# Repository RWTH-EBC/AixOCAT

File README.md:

# AixOCAT - Library framework for building automation systems based on the OSCAT libraries

AixOCAT is an open source software library for the implementation of control algorithms in building automation systems and test benches and is based on the [OSCAT](http://www.oscat.de/) libraries.

As the library framework is developed at the [RWTH Aachen University, E.ON Energy Research Center, Institute
for Energy Efficient Buildings and Indoor Climate](https://www.ebc.eonerc.rwth-aachen.de/cms/~dmzz/E-ON-ERC-EBC/?lidx=1), the library's name AixOCAT is derived from the city's French 
name Aix-la-Chapelle, which the people of Aachen are very fond of and use a lot. 
With the name AixOCAT we follow this local tradition.

AixOCAT features support for different software tools, that can be used for the implementation of control algorithms, as well as support for various commonly used communication/signal transmission interfaces.

This GitHub page will be used to further develop the package and make it
available under the
[MIT License](LICENSE).

If you have any questions regarding AixOCAT feel free to contact us at
[ebc-aixocat@eonerc.rwth-aachen.de](mailto:ebc-aixocat@eonerc.rwth-aachen.de).

---

## Description

- Evaluation and interfaces for different tools that can be used for the implementation of control algorithms
- Examples and documentation for different communication/signal transmission interfaces
- General control modules for different use cases 

## Version

AixOCAT is an ongoing research project, the current version is 1.0.0, which is
still a pre-release.

## How to use AixOCAT

### Dependencies

Visual Studio is required.

### Installation Guide

Library Installation in [TwinCAT 3](https://infosys.beckhoff.com/english.php?content=../content/1033/tc3_plc_intro/27021601982523403.html)

Library Installation in [Codesys](https://help.codesys.com/webapp/_cds_struct_installing_libraries;product=codesys;version=3.5.12.0)

If you actively develop AixOCAT you can clone this repository by using:

 `git clone [SSH-Key/Https]`

### How to contribute to the development of AixOCAT
You are invited to contribute to the development of AixOCAT. You may report any issues by using the 
[Issues](https://github.com/RWTH-EBC/AixOCAT/issues) button.
Furthermore, you are welcome to contribute via [Pull Requests](https://github.com/RWTH-EBC/AixOCAT/pulls).
The workflow for changes is described in our [contribution guidelines](CONTRIBUTING.md).

### AixOCAT related publications

- [AixOCAT: Open-Source-Bibliothek für Automationssysteme](Resources/Documentation/AixOCAT_paper_FB_RWTH.pdf)

## License

AixOCAT is released by RWTH Aachen University, E.ON Energy
Research Center, Institute for Energy Efficient Buildings and Indoor Climate,
under the
[MIT License](LICENSE).

## Acknowledgements

As this framework is based on the OSCAT libraries we want to acknowlegde Tobias Mühlbauer for his Contribution to the OSCAT libraries.

We also acknowledge the ERDF for their financial support (reference No. KEU-1-006C).

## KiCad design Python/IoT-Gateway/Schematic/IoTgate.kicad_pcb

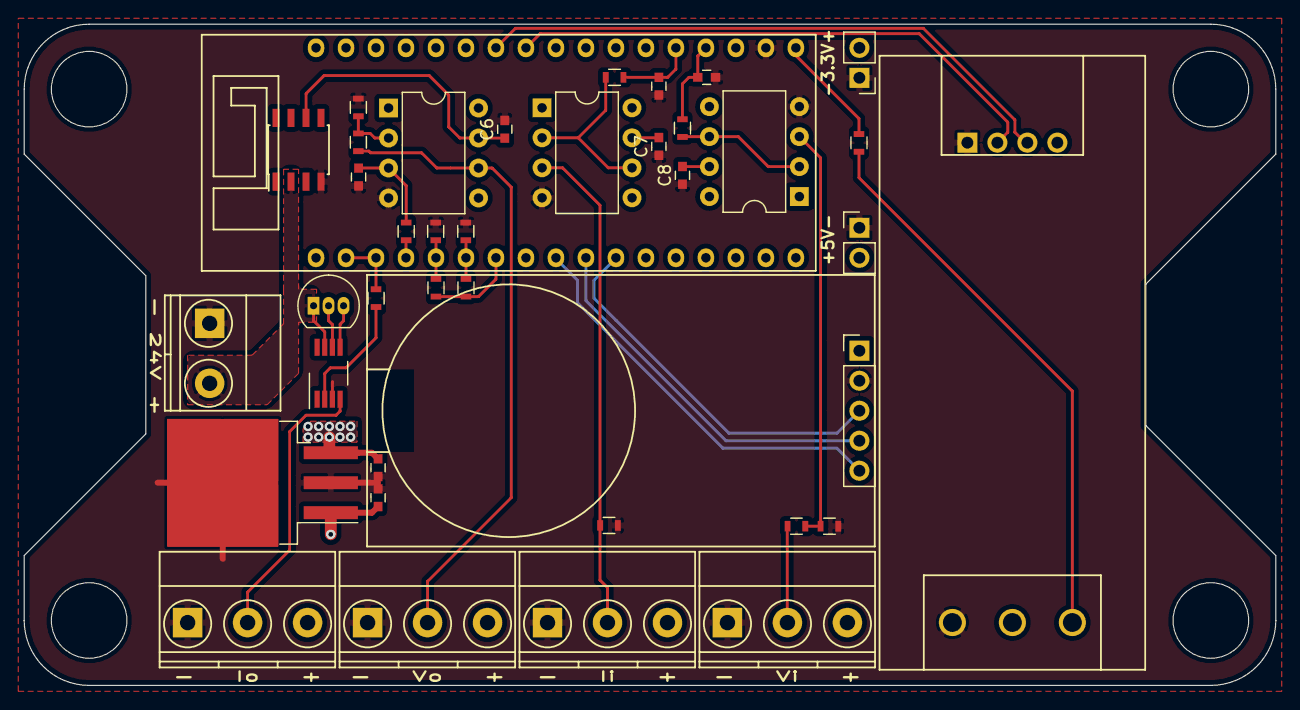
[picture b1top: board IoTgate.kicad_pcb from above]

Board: 2 copper layers, 106.0 x 56.0 mm, 39 parts (0 on the bottom side), 30 nets.

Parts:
C1: 220n; C_0603
C2, C6, C7, C8: 100n; C_0603
C3, C4, C5: 1μF; C_0603
J1: Conn_01x02; TerminalBlock_2pol
J3, J4, J5, J6: Conn_01x03; TerminalBlock_3pol
J8, J9: Conn_01x02; Socket_Strip_Straight_1x02_Pitch2.54mm
Q1: BC337; TO-92_Inline_Narrow_Oval
R1, R3: 2MΩ; R_0603
R2, R4: 1MΩ; R_0603
R5, R6, R7, R9: 10kΩ; R_0603
R8: 15kΩ; R_0603
R10: 680 Ω; R_0603
R11: 22kΩ; R_0603
R12: 3.3kΩ; R_0603
R13: 45.3Ω; R_0603
R14: 33kΩ; R_0603
U1: LM3405-5.0; TO-263-3_TabPin2
U2: ESP-32-PICO-KIT-V4; ESP32v4
U3: REF102AU; SOIC-8_3.9x4.9mm_Pitch1.27mm
U4: ds1302module; ds1302
U5: xy-017
U6, U7: OPA344PA; DIP-8_W7.62mm
U8: OPA705PA; DIP-8_W7.62mm
U9: XTR117; VSSOP-8_3.0x3.0mm_Pitch0.65mm

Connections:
+3V3: J9.2, R10.2, U2.1, U4.1, U5.4
+5V: C2.1, C7.2, C8.2, J8.2, U1.3, U2.34, U6.7, U7.7
+10V: C6.1, U3.6, U8.7
+24V: C1.2, J1.2, J3.3, J4.3, J5.3, J6.3, Q1.1, U1.1, U3.2, U9.7
/Iin: C4.1, R7.2, U2.5
/Iout: R8.2, U2.19, U2.20
/RxD: U2.10, U5.2
/TxD: U2.11, U5.3
/Vin: C3.1, R6.2, U2.4
/Vout: R5.2, U2.21
/Vref: R1.1, R2.1, U2.24
/Vref-1.3: R1.2, R4.2, U2.23
/Vref-2.3: R2.2, R3.2, U2.22
GND: C1.1, C2.2, C3.2, C4.2, C5.2, C6.2, C7.1, C8.1, J1.1, J3.1, J4.1, J5.1, J6.1, J8.1, J9.1, R3.1, R4.1, R9.2, R12.1, R13.2, U1.2, U2.2, U3.4, U4.2, U5.1, U5.7, U6.4, U7.4, U8.4, U9.3
unnamed: C5.1, R5.1, U8.3
unnamed: J3.2, R14.1
unnamed: J4.2, R13.1, U7.3
unnamed: J5.2, R11.1, U8.6
unnamed: J6.2, U9.4
unnamed: R10.1, U5.5
unnamed: Q1.2, U9.6
unnamed: Q1.3, U9.5
unnamed: R6.1, U6.2, U6.6
unnamed: R7.1, U7.2, U7.6
unnamed: R8.1, U9.2
unnamed: R9.1, R11.2, U8.2
unnamed: R12.2, R14.2, U6.3
unnamed: U2.26, U4.5
unnamed: U2.27, U4.4
unnamed: U2.28, U4.3

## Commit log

2018-04-11 add EBC_Logo.png
2018-04-11 first draft of folder structure
2018-04-11 update lolo path
2018-04-11 update logo path 2. try
2018-04-11 Beispiel: Steuerung WP Prüfstand
2018-04-11 Create LICENSE
2018-04-11 Contains internal information
2018-04-11 move LICENSE and some md files
2018-04-11 Need for license
2018-04-11 add oscat basic, network and building
2018-04-11 Rename CONTRIBUTING.md to git_CONTRIBUTING.md
2018-04-11 name changed to OSCAT
2018-04-11 Added link to external library installation docs
2018-04-11 Naming of example project changed to English. Placeholders for csv paths. readme.txt added
2018-04-17 Fixed tcm file naming issue in example project
2018-04-17 Fixed another naming issue in example project
2018-09-04 Modbus RTU documentation and sample project added
2018-10-19 Modbus readme updated
2019-02-01 Added ISARC files
2019-02-18 Added testhall usecase for AixOCAT paper
2019-04-02 Add WiloPumpFunction library
2019-05-07 Changed structure and updated content
    New structure:
    Examples: Basic examples that are standalone and do not provide further
    functions or packages
    Interfaces: Software interfaces for integrating Python, Modelica etc. on
    Beckhoff PLC
    OSCAT: OSCAT library
2019-08-09 corrected the grammar and some other small changes
2019-09-24 deletion of beckhoff networks (too many errors)
2019-09-24 FB_PID reworked
2020-02-07 Added ERDF funding reference and logo.
2020-04-15 Update redme.md
    add AixOCAT publication
2020-07-02 #39 bug fix in FT_PID.TcPOU
2020-10-22 No anti-wind up is applied when PID is reset.
2020-10-23 FB_PID now doesn't apply anti-wind up on reset and accepts an offset value for Y.
2020-10-23 Raised version number to 1.0.3
2020-10-23 Untrack some unnecessary files.
2020-10-23 FB_PID: Reset the Integrator when providing an initial value for Y and providing RST as TRUE.
2020-10-23 Additional changes to .gitignore
2020-10-23 New build of library.
2020-10-23 Small change to FB_PID behaviour when setting a Y offset.
2020-11-03 Initial Commit of VBAixGUI
    Initial commit of the VBAixGUI Library to enable the fast creation of a VB.NET based GUI application with the use of ADS as communication protocol.
2020-11-03 new library file including last merge
2020-11-03 added .vs to gitignore
2020-11-03 Changed project from XAE type to PLC type.
2020-11-04 added gitignore for python, pycharm, TwinCat
2020-11-06 Added some additional functions for accessibility.
2020-11-09 Buffer/ConvergenceWatchdog now use Math.Abs()
    Deviations are now always evaluated and/or displayed with Math.Abs()
2020-11-09 Added an additional REV input variable, which flips the inputs.
2020-11-10 Updated AssemblyInfo.
2020-11-10 Created the extended delay with 200 cycles.
2020-11-10 Fixed a merge error.
2020-12-07 Added some SubmitSetValue() Functions to enable a forced update
2021-01-12 Included yOffset in Anti-wind up calculation
2021-02-16 Removed ISARC files
    New location: https://github.com/RWTH-EBC/IoT-Gateway
2021-02-23 Delete OSCAT.library
    only master branch should include the binary file
2021-02-23 Added oscat documentation files
2021-02-23 added network lib to oscat
2021-02-23 deleted .vs of heat circle example
2021-02-23 changed project version to 1.1.1
2021-02-23 Added new compiled library file v1.1.1
2021-02-24 WIP: outline of MQTT ADS interface
    The interface shall feature multi-threading to process incoming messages
    and outgoing messages in parallel. ADS and MQTT will be seperated
    classes and data should be transferred from one instance to the other
    while being parsed according to the data point handling.
2021-03-05 Add TON_P Function Block #65
2021-03-05 Add PR-workflow #67
2021-03-06 Added sample GVL and prepare variable isolation
2021-03-07 Integrated TON_P POU into OSCAT library
2021-03-07 Create pub/sub variable lists from ADS variables
2021-03-17 Enhanced MQTT connection
2021-03-19 Enhanced ADS connection
    - Further implemented ADS connection to PLC application
    - Added JSON parsing
2021-03-19 Minor changes, added first draft of exception handling
2021-03-22 added pycharm folder to gitignore
2021-03-24 Removed own threading and refurbishment
    - removed the own threading implementation, now the internal threading
    mechanism of the mqtt module is used
    - added ads write function to allow writing mqtt values to the plc
    - implemented gathering ads variables by symbols directly out of the ads
    connection
    - added handles in the generated pub and sub dicts to speed up reading
2021-03-25 Added config, did some debugging and fixed errors
2021-03-25 Added create_route to config
2021-03-28 Working version with aedifion connection
    - Updated structure for connecting and publish/subscribe to aedifion
    Tested three scenarios:
    1. Local broker and PLC application (working!)
    2. Local broker and remote PLC application (working!)
    3. Remote broker and remote PLC application (publish is working,
    subscribe probably)
2021-03-29 Enhanced documentation
    - Enhanced documentation of the interface class
    - Removed some unnecessary code
    - Added an mqtt_stop function
2021-03-31 Updating version dependencies of pyads
2021-05-26 Modified .gitignore to ignore confidential config
2021-05-26 added setup.py to install necessary packages via pip
2021-05-26 small changes in setup.py
2021-05-26 config.ini for direct testing - open-source broker and localhost Net-ID
2021-05-26 change names of example TwinCat Script
2021-05-26 Add neutral colored logo with @Janine-B
2021-05-26 Add neutral color logo with @Janine-B
2021-05-26 Update logo made with @Janine-B
2021-05-26 Shrink ERDF logo a bit
2021-05-26 Add relative link to new contributions guidelines
2021-05-26 Make link to license file also relative
2021-05-27 small error in .tsproj file caused by incorrect save
2021-05-27 added .bak-files to gitignore
2021-05-27 deleted further files
2021-05-27 Added Coriolis-Sensor to Libary
2021-05-27 Added Compressor (including gif)
2021-06-02 Add AixOCAT german paper
2021-06-02 Add updated german paper reference to publications
2021-06-14 [ERN] add function in 'parsing_and_assignment' to read variables marked by identifier
2021-06-18 Input_SetValue: Added Property "Decimal Places"
2021-06-18 Input_SetValue: Added Property "Increment"
2021-06-22 Add a timeout variable
    Check for timeout during connection check by evaluating a thrown Exception.
2021-06-22 Clear imports
2021-06-22 Fix timeout reset on forced connection attempt
2021-06-23 Translated Compressor Properties to English
2021-06-23 Translated everything to English
2021-06-29 [ERN] add function to read symbols by identifier
2021-06-30 added print command to publish function
2021-06-30 changed function to get symbols for testing
2021-06-30 changed input class to own ads class
2021-06-30 small changes for testing get symbols by marker
2021-06-30 [ERN] Identifier '#' does not have to stand alone in the comment
2021-07-02 Transparent Gifs
2021-07-02 Added Inkscape Templates and removed pipes
2021-07-06 Added Diagram Element
2021-07-14 New Properties to Diagram Element
2021-08-09 Add two new DataTypes for control parameter set and IO Terminal Signal conversion
2021-08-09 Rename folder CO_Nversion to Conversion
2021-08-09 Add IO Terminal function blocks
    Add additional arithmetic average over up to 200 values
2021-08-09 Add a generic controller function block
    Add a voltage controlled fan function block
2021-08-10 Added "Sammlung" in Diagram
2021-08-10 Added Datapoints, TODO: Remove Series
2021-08-11 Fixed: Delete Series
2021-08-11 Added Marker Properties in Diagram
2021-08-20 Fixed Background Picture in Diagram
2021-08-31 Fix class references
2021-08-31 Update copyright year
2021-08-31 Fix Reference
2021-09-07 Fix fan controller
2021-10-12 Marker Style Hardcoded
2021-11-02 Add first version
2022-02-04 Changed SymbolsLoadMode in connect from .Flat to .VirtualTree #86
2022-02-16 Move FAN_VOLTAGE_CONTROL to VOLTAGE_CONTROL
2022-02-16 Add icons
2022-02-16 Add mixing and control valve
2022-03-29 Add Testsuite for HSSController FB
2022-03-29 Add test program
2022-03-31 Add Test Method To FB_HSSController TestSuite
2022-04-03 Clarify instructions for contributions
2022-04-04 Add TestSuite for FC_HeatingCurve
2022-04-05 Add Test Cases for FC_HeatingCurve
2022-04-12 Add tests to plc task #89
2022-05-19 Fix measurement duration and resolution set
2022-05-23 Fix resolution property function
2022-08-17 Update Changes from Fork-Repo
2022-08-17 Revert "Merge branch '91-hil3-gui' into origin/91-hil3-gui"
    This reverts commit 702a704c306e5889dc16b4e8788f7f05676f94f7.
2022-08-17 Updated to develop Branch from Fork-Repo
2022-11-02 Add saving of intermediate measurement points
    Increase maximum duration to one day
2022-11-02 Add additional switch to activate/deactivate intermediate saving
2022-11-02 Activate cached only mode only for fast paced measurements
2023-10-17 Add new anti-windup strategy
2023-10-17 Add initial value for integrator reset
2023-10-17 Reformat file
2023-10-17 Add short explanation of anti windup strategy
2024-01-02 new compiled lib file
2025-11-28 added ACSenLib
2025-11-28 Added temp sensor
2025-11-28 added interface
2025-12-01 added relevant sensors from HiL1 project
